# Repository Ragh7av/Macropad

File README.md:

<h1 align="center">Macropad</h1> 
<div align="center">         
<p align="center">

A custom 6-key custom macropad with a rotary encoder, Cherry MX red mechanical switches, a custom PCB, and a 3D-printed case to take your workflow to the next level.
</p>
https://cad.onshape.com/documents/96bc1078680b64831b101746/w/834816f7826d3f1ee40a2d83/e/93c4e7053cae44b7b10a563c?renderMode=0&uiState=6a3fa3953d8bda3797197edf
<h1 align="center">Overview</h1>
        
<p align="center">This project is a custom desktop macropad built around the RP2040-Zero. It includes 6 Cherry MX Red mechanical switches for satisfying tactile sounds while clocking, a KY-040 rotary encoder for volume or scroll control, a custom-designed PCB, and a sleek 3D-printed two-part enclosure. 

# Repository Contents

| Path | What it contains |
| --- | --- |
| [`3D_PRINTS`](https://github.com/Ragh7av/Macropad/tree/main/3D_PRINTS) | STL files for quick access to 3D printing the top and bottom enclosure halves |
| [`ASSEMBLY`](https://github.com/Ragh7av/Macropad/tree/main/ASSEMBLY) | Files related to the mechanical assembly of the macropad |
| [`BOM`](https://github.com/Ragh7av/Macropad/tree/main/BOM) | Bill of materials details and cost breakdowns |
| [`FIRMWARE`](https://github.com/Ragh7av/Macropad/tree/main/FIRMWARE) | Firmware code (C++/CircuitPython/KMK) to program the keys and encoder |
| [`GERBERS`](https://github.com/Ragh7av/Macropad/tree/main/GERBERS) | Ready-to-manufacture Gerber files for fabricating the PCB |
| [`IMAGES`](https://github.com/Ragh7av/Macropad/tree/main/IMAGES) | Photos and screenshots of the project |
| [`PCB`](https://github.com/Ragh7av/Macropad/tree/main/PCB) | KiCad schematic and PCB layout files |
| [`ZINE`](https://github.com/Ragh7av/Macropad/tree/main/ZINE) | Project zine documentation |
| [`CAD`](CAD) | Project 3D models |

<h1 align="center">Why am I even building this?</h1>
<p align="center">
 I built this project as a part of an event called <a href="https://fallout.hackclub.com">Fallout</a>, organized by a non-profit organization called <a href="https://hackclub.com">Hack Club</a>. We build and ship hardware projects, and for that, we get some cool gifts and grants to build it IRL. After building hardware projects for 60 hours, we get invited to Shenzhen, China for a Hardware Hackathon. I am building this project to work toward those 60 hours.
 </p>

<h1 align="center">Why Macropad?</h1>

So I spend a lot of time at my desk doing coding, editing, and general productivity tasks. I frequently need quick access to specific shortcuts, media controls, and repetitive keystrokes that are tedious to execute on a standard keyboard. I created this project  to solve these problems and help myself get supercalifragilisticexpialidocious in building super cool hardware things while optimizing my workflow. 

# Zine 

# Printed Circuit Board (PCB)

#  Schematic

# CAD

<h1 align="center">The Features</h1>
</div>

1. **6 Programmable Keys**: Features 6 Cherry MX Red linear mechanical switches for smooth, fast, and customizable keystrokes (copy/paste, media navigation, macro strings, etc.).
2. **Rotary Encoder**: Includes a built-in KY-040 rotary encoder with a push-button function, perfect for controlling system volume, zooming, or scrolling through timelines.
3. **Custom PCB**: A printed circuit board routing the switches and encoder directly to the RP2040-Zero while looking beautiful with a custom silkscreen designs.
4. **RP2040-Zero Brains**: Powered by the compact Raspberry Pi RP2040-Zero microcontroller, ensuring fast response times and easy programmability.
5. **3D Printed Enclosure**: A custom-designed two-part (top and bottom) FDM 3D-printed case to keep the electronics safe and look great on a desk.

<div align="center">   

</div>

# The Components Used

1. RP2040-Zero (Raspberry Pi Microcontroller)
2. KY-040 Rotary Encoder Module
3. Cherry MX RED mechanical switches (x6)
4. PBT DSA Blank Keycaps for MX Switches (x6)
5. Custom Printed Circuit Board (PCB)
6. 3D Printed Case (Top and Bottom halves)

# Bill of Materials

| Component Name | Quantity | Price (₹) | Total Cost (₹) | Shipping (₹) | Total Price (₹) |
| --- | --- | --- | --- | --- | --- |
| PCB (Robu PCB Manufacturing) | 1 | ₹180 | ₹900 | ₹49 | ₹949 |
| Keycaps for MX keys (ATORSE 12Pcs Blank) | 6 | ₹52.25 | ₹627 | Free | ₹627 |
| Cherry MX RED mechanical keys | 6 | ₹44.9 | ₹449 | Free | ₹449 |
| Raspberry Pi RP2040 Zero | 1 | ₹235 | ₹235 | ₹24.5 | ₹259.5 |
| KY-040 Rotary encoder | 1 | ₹59 | ₹59 | ₹24.5 | ₹83.5 |
| Case bottom half (at 40% infill) | 1 | ₹159 | ₹159 | ₹49.5 | ₹208.5 |
| Case top half (at 40% infill) | 1 | ₹90 | ₹90 | ₹49.5 | ₹139.5 |
| **Subtotal** | | | **₹2519** | **₹197** | **₹2716** |

# How to Build it?

**To replicate, follow the steps below:**
1) First, grab the PCB Gerber files from the `GERBERS` folder and send them to your preferred PCB manufacturer (like Robu, JLCPCB, etc.).
2) Next, grab the 3D models from the `3D_PRINTS` folder and print the top and bottom case halves (recommended 40% infill for a solid feel).
3) Purchase the parts mentioned in the **BOM**.
4) Solder the RP2040-Zero, Cherry MX switches, and the rotary encoder onto your fabricated PCB.
5) Flash the firmware from the `FIRMWARE` folder onto your RP2040-Zero via USB-C.
6) Test the keys and encoder on your computer to ensure all keystrokes register. 
7) Assemble the PCB into the 3D-printed shell, pop on your keycaps, and secure everything together!

## Firmware setup
 - Connect your RP2040-Zero to your computer via USB-C.
 - If using Arduino IDE: Select the appropriate RP2040 board under Tools > Board, select the Port, compile, and click Upload.
 - Customize your keybindings in the firmware code to map to your preferred macros, shortcuts, or media controls before uploading.

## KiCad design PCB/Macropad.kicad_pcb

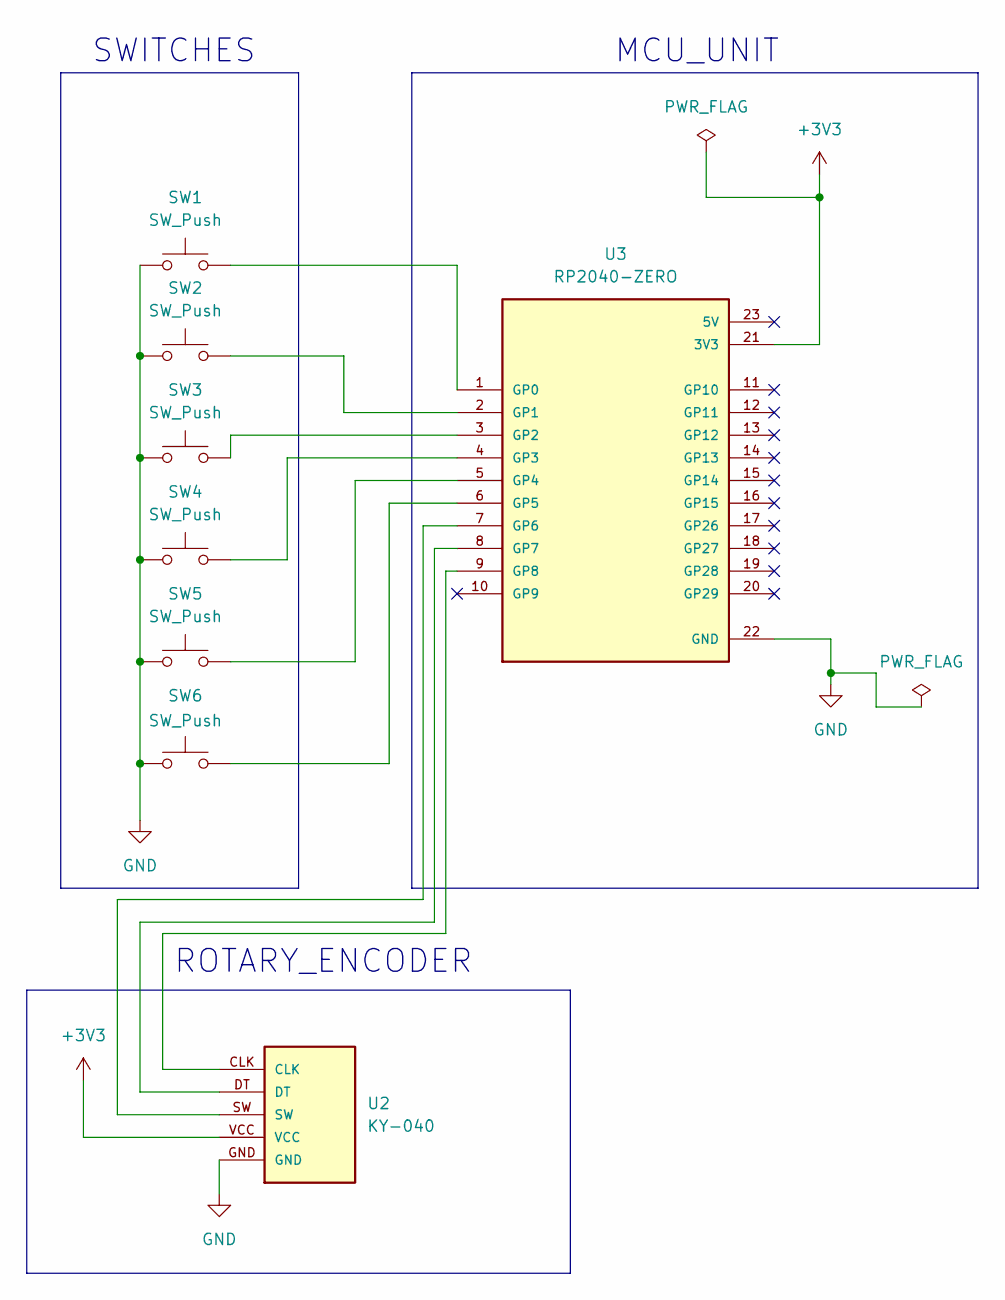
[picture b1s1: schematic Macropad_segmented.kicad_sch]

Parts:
SW1, SW2, SW3, SW4, SW5, SW6: SW_Push; SW_Cherry_MX_1.00u_PCB
U2: KY-040; KY-040-PORT
U3: RP2040-ZERO; FP_RP2040; PARTREV NA

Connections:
+3V3: U2.VCC, U3.21 (3V3)
GND: SW1.1, SW2.1, SW3.1, SW4.1, SW5.1, SW6.1, U2.GND, U3.22 (GND)
unnamed: SW1.2, U3.1 (GP0)
unnamed: SW2.2, U3.2 (GP1)
unnamed: SW3.2, U3.3 (GP2)
unnamed: SW4.2, U3.4 (GP3)
unnamed: SW5.2, U3.5 (GP4)
unnamed: SW6.2, U3.6 (GP5)
unnamed: U2.SW, U3.7 (GP6)
unnamed: U2.DT, U3.8 (GP7)
unnamed: U2.CLK, U3.9 (GP8)

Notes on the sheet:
ROTARY_ENCODER
SWITCHES
MCU_UNIT

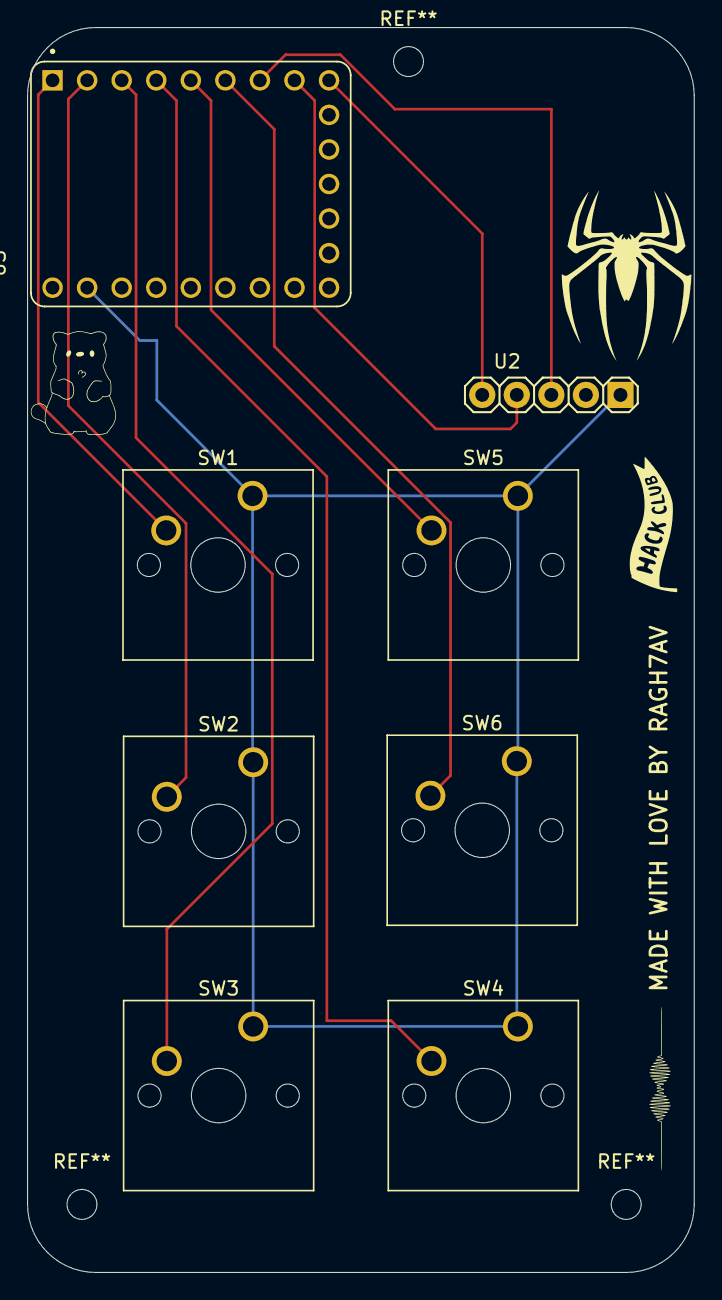
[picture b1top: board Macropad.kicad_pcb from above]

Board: 2 copper layers, 49.0 x 91.5 mm, 8 parts (0 on the bottom side), 11 nets.

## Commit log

2026-06-20 Create ASSETS
2026-06-20 Create BOM1
2026-06-20 Create NVM
2026-06-20 Create QMK
2026-06-20 Create HEEHEEEEE
2026-06-20 Create MEOW
2026-06-20 Create RAWR
2026-06-20 Create SWIM
2026-06-25 Rename BOM1 to BOM.csv
2026-06-25 Add Macropad project files with LFS
2026-06-27 Update PNGs and project files
